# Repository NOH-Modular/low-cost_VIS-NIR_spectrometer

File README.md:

# Low Cost VIS/NIR Spectrometer
We are a team of three students as part of Glasgow University's ENG5026 Design Special Topic 5. This class puts students in groups to initially design a proof of concept and ultimately a product in collaboration with research taking place at the University.

We aim to design a miniaturised, low-cost visible light and near-infrared spectrometer in a handheld form-factor to analyse fruit ripeness and other VIS/NIR applications including use in schools and universities. Existing products are found in the range of between £400-1000 and we aim to produce an alternative which will be more affordable and accessible.

Currently, the project consists of a custom RP2040 microcontroller board with an e-paper display to minimise power draw. The spectral sensing will use AMS-OSRAM's spectral sensor chips which has shown positive results in testing but in order to provide a more robust and elegant solution, additional funding will allow us to experiment with better sensors. The AS7265x triad sensors will give the widest possible range of sensing while still being affordable to the end user.

As well as being low-cost, it is an aim of the project to achieve long battery life for portable use. This is why low-power design such as battery management and an e-paper display has been at the forefront of component choice.

The final output (a PCB with surface-mount components pre-assembled) will be very low-cost, but we require funding for prototyping and testing various spectrometer chips, battery management, microcontrollers, and LEDs.

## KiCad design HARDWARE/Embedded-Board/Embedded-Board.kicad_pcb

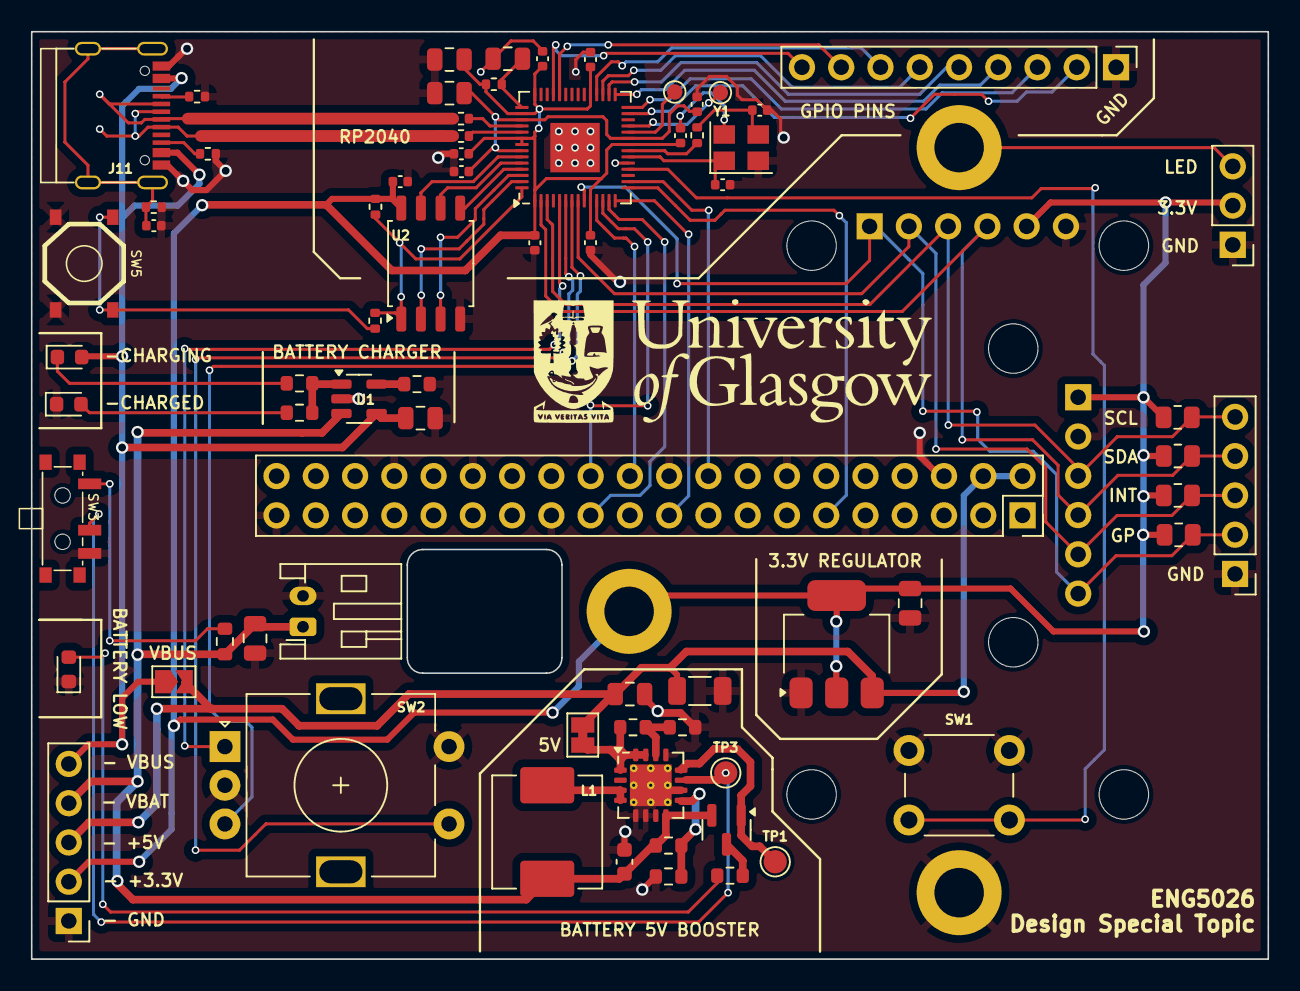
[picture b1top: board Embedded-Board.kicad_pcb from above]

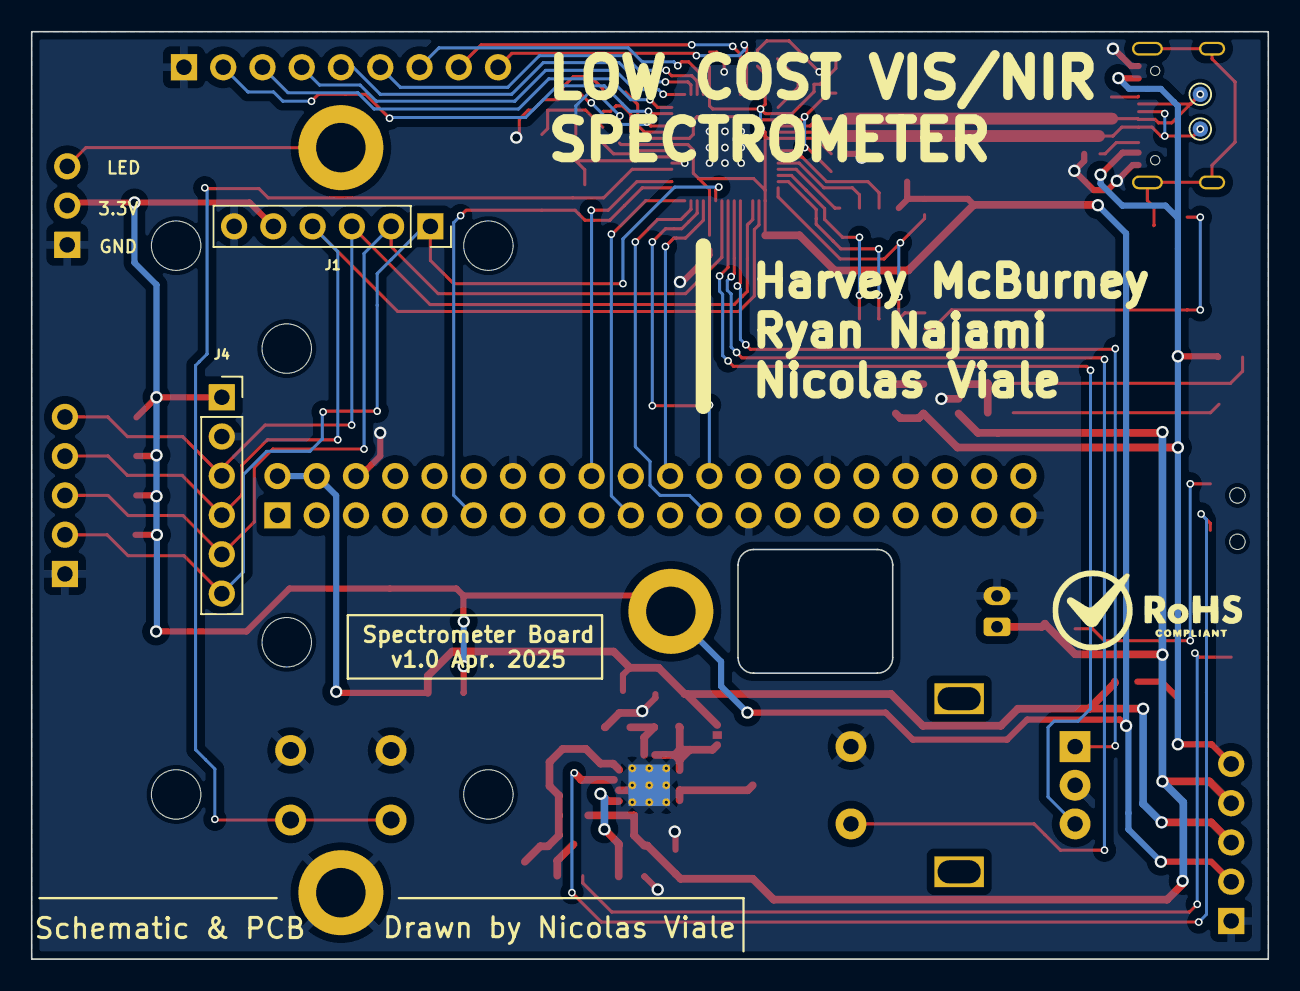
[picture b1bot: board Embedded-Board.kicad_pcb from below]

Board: 2 copper layers, 80.0 x 60.0 mm, 75 parts (4 on the bottom side), 61 nets.

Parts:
BT1: Battery_Cell; JST_PH_S2B-PH-K_1x02_P2.00mm_Horizontal
C2, C3, C58: 10u; C_0805_2012Metric
C4: 100n; C_0603_1608Metric
C5, C13, C14, C21: 2.2u; C_0805_2012Metric
C6: 100u/6V; C_1206_3216Metric
C8, C11, C12, C15, C16, C17, C18, C19, C20, C34: 100n; C_0402_1005Metric
C48, C68: 33p; C_0402_1005Metric
D1: orange; LED_0603_1608Metric
D2: green; LED_0603_1608Metric
D3: red; LED_0603_1608Metric
J1: AD7265X; PinSocket_1x06_P2.54mm_Vertical
J2: POWER-pins; PinHeader_1x05_P2.54mm_Vertical
J3: Conn_02x20_Odd_Even; PinSocket_2x20_P2.54mm_Vertical
J4: AD7341; PinSocket_1x06_P2.54mm_Vertical
J5: I2C comm; PinHeader_1x05_P2.54mm_Vertical
J6: GPIO PINS; PinHeader_1x09_P2.54mm_Vertical
J7: BOARD->LED; PinHeader_1x03_P2.54mm_Vertical
J11: USB_C_Receptacle_USB2.0; USB-C-JLCPCB
JP1: VBUS-5V; SolderJumper-2_P1.3mm_Open_TrianglePad1.0x1.5mm
JP2: OUT-5V; SolderJumper-2_P1.3mm_Bridged_Pad1.0x1.5mm
L1: 6.8u; L_APV_APH0630
Q1: MMUN2133LT1G; SOT-23
R1, R2, R21, R22: 4.7k; R_0805_2012Metric
R3: 10k; R_0402_1005Metric
R4, R5: 1k; R_0402_1005Metric
R6: 470; R_0603_1608Metric
R7: 200; R_0402_1005Metric
R8, R20: 1k; R_0603_1608Metric
R9: 2k; R_0603_1608Metric
R10, R18: 1.85M; R_0603_1608Metric
R11, R17: 340k; R_0603_1608Metric
R12: 220; R_0402_1005Metric
R13, R14: 5.1k; R_0402_1005Metric
R15, R16: 27; R_0402_1005Metric
R19: 200k; R_0603_1608Metric
SW1: SW_Push; SW_PUSH_6mm_H13mm
SW2: RotaryEncoder_Switch; RotaryEncoder_Alps_EC11E-Switch_Vertical_H20mm
SW3: SW_Push_SPDT; Alps-Alpine-SPDT
SW5: BOOT; JLC-BASIC-BUTTON
TP1: LBO; TestPoint_Pad_D1.5mm
TP3: EN; TestPoint_Pad_D1.5mm
TP4: D-; TestPoint_Pad_D1.0mm
TP5: D+; TestPoint_Pad_D1.0mm
TP6: SWCLK; TestPoint_Pad_D1.0mm
TP7: SWD; TestPoint_Pad_D1.0mm
U1: MCP73831-2-OT; SOT-23-5
U2: W25Q16JVS; SOIC-8_5.3x5.3mm_P1.27mm
U3: RP2040; QFN-56-1EP_7x7mm_P0.4mm_EP3.2x3.2mm
U4: TPS61090; Texas_RSA_VQFN-16-1EP_4x4mm_P0.65mm_EP2.7x2.7mm_ThermalVias
U18: LM1117-3.3; SOT-223-3_TabPin2
Y1: 12MHz; Crystal_SMD_3225-4Pin_3.2x2.5mm

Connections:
+1V1: C11.1, C12.1, C13.1, U3.23 (DVDD), U3.45 (VREG_VOUT), U3.50 (DVDD)
+3.3V: C8.1, C14.1, C15.1, C16.1, C17.1, C18.1, C19.1, C20.1, C58.1, J1.5, J2.2, J4.1, J7.2, R1.1, R2.1, R3.1, R7.1, R21.1, R22.1, U2.8 (VCC), U3.1 (IOVDD), U3.10 (IOVDD), U3.22 (IOVDD), U3.33 (IOVDD), U3.42 (IOVDD), U3.44 (VREG_IN), U3.48 (USB_VDD), U3.49 (IOVDD), U18.2 (VO)
+5V: C5.1, C6.1, J2.3, J3.2, J3.4, JP1.2 (B), JP2.2 (B), U18.3 (VI)
+VBAT: BT1.1 (+), C3.1, C4.1, J2.4, L1.1, Q1.2 (E), R10.2, R17.2, U1.3 (V_{BAT}), U4.8 (VBAT)
E-PAPER-BUSY: J3.18, U3.16 (GPIO13)
E-PAPER-CS: J3.24, U3.12 (GPIO9)
E-PAPER-DC: J3.22, U3.11 (GPIO8)
E-PAPER-MOSI: J3.19, U3.14 (GPIO11)
E-PAPER-RST: J3.11, U3.15 (GPIO12)
E-PAPER-SCK: J3.23, U3.13 (GPIO10)
ENC-A: SW2.A, U3.5 (GPIO3)
ENC-B: SW2.B, U3.7 (GPIO5)
ENC-PSH: SW2.S1, U3.6 (GPIO4)
GND: BT1.2 (-), C2.2, C3.2, C4.2, C5.2, C6.2, C8.2, C11.2, C12.2, C13.2, C14.2, C15.2, C16.2, C17.2, C18.2, C19.2, C20.2, C21.2, C34.2, C48.1, C58.2, C68.2, D2.1 (K), D3.1 (K), J1.6, J2.1, J3.6, J3.9, J3.14, J3.20, J3.25, J3.30, J3.34, J3.39, J4.2, J5.1, J6.1, J7.1, J11.A1 (GND), J11.B1 (GND), R9.2, R11.1, R12.2, R13.2, R14.1, R19.2, SW1.1, SW2.C, SW2.S2, SW3.3 (C), SW5.2, U1.2 (V_{SS}), U2.4 (GND), U3.19 (TESTEN), U3.57 (GND), U4.5 (PGND), U4.6 (PGND), U4.7 (PGND), U4.10 (SYNC), U4.13 (GND), U4.17 (PAD), U18.1 (GND), Y1.2, Y1.4
unnamed: C68.1, R5.1, Y1.3
unnamed: D1.1 (K), R6.1
unnamed: D2.2 (A), R8.1
unnamed: D3.2 (A), R20.2
unnamed: J6.2, U3.27 (GPIO16)
unnamed: J6.3, U3.28 (GPIO17)
unnamed: J6.4, U3.29 (GPIO18)
unnamed: J6.5, U3.30 (GPIO19)
unnamed: J6.6, U3.31 (GPIO20)
unnamed: J6.7, U3.32 (GPIO21)
unnamed: J6.8, U3.38 (GPIO26_ADC0)
unnamed: J6.9, U3.39 (GPIO27_ADC1)
unnamed: J11.A5 (CC1), R13.1
unnamed: J11.B5 (CC2), R14.2
unnamed: J11.A6 (D+), J11.B6 (D+), R16.2, TP5.1
unnamed: J11.A7 (D-), J11.B7 (D-), R15.1, TP4.1
unnamed: C34.1, J11.S1 (SHIELD), R12.1
unnamed: JP2.1 (A), R18.2, U4.1 (VOUT), U4.15 (VOUT), U4.16 (VOUT)
unnamed: L1.2, U4.3 (SW), U4.4 (SW)
unnamed: Q1.1 (B), TP1.1, U4.12 (LBO)
unnamed: Q1.3 (C), R20.1
unnamed: R4.1, SW5.1
unnamed: R17.1, SW3.1 (A)
unnamed: SW3.2 (B), TP3.1, U4.11 (EN)
unnamed: R9.1, U1.5 (PROG)
unnamed: R6.2, R8.2, U1.1 (STAT)
unnamed: U2.6 (CLK), U3.52 (QSPI_SCLK)
unnamed: U2.5 (DI(IO0)), U3.53 (QSPI_SD0)
unnamed: U2.2 (DO(IO1)), U3.55 (QSPI_SD1)
unnamed: U2.3 (IO2), U3.54 (QSPI_SD2)
unnamed: U2.7 (IO3), U3.51 (QSPI_SD3)
unnamed: R3.2, R4.2, U2.1 (~CS), U3.56 (QSPI_SS)
unnamed: C21.1, R7.2, U3.43 (ADC_AVDD)
unnamed: TP6.1, U3.24 (SWCLK)
unnamed: TP7.1, U3.25 (SWD)
unnamed: C48.2, U3.20 (XIN), Y1.1
unnamed: R5.2, U3.21 (XOUT)
unnamed: R18.1, R19.1, U4.14 (FB)
unnamed: R10.1, R11.2, U4.9 (LBI)
PUSH-SWITCH: SW1.2, U3.18 (GPIO15)
SENSOR-INT: J1.2, J4.5, J5.3, R21.2, U3.8 (GPIO6)
SENSOR-RST: J1.1, J4.6, J5.2, R22.2, U3.9 (GPIO7)
SENSOR-SCL: J1.3, J4.3, J5.5, R1.2, U3.3 (GPIO1)
SENSOR-SDA: J1.4, J4.4, J5.4, R2.2, U3.2 (GPIO0)
USB_D+: R16.1, U3.47 (USB_DP)
USB_D-: R15.2, U3.46 (USB_DM)
VBUS: C2.1, D1.2 (A), J2.5, J11.A4 (VBUS), J11.B4 (VBUS), JP1.1 (A), U1.4 (V_{DD})

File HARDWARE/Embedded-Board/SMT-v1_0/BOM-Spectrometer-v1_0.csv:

Comment,Designator,Footprint,LCSC Part Number
Battery_Cell,BT1,Connector_JST:JST_PH_S2B-PH-K_1x02_P2.00mm_Horizontal,C5359610
100n,C4,Capacitor_SMD:C_0603_1608Metric,C14663
100u/6V,C6,Capacitor_SMD:C_1206_3216Metric,C15008
10u,"C2,C3,C58",Capacitor_SMD:C_0805_2012Metric,C15850
USB_C_Receptacle_USB2.0,J11,userr:USB-C-JLCPCB,C165948
6.8u,L1,Inductor_SMD:L_APV_APH0630,C5349706
MMUN2133LT1G,Q1,Package_TO_SOT_SMD:SOT-23,C86182
10k,R3,Resistor_SMD:R_0402_1005Metric,C25744
470,R6,Resistor_SMD:R_0603_1608Metric,C23179
200,R7,Resistor_SMD:R_0402_1005Metric,C25087
2k,R9,Resistor_SMD:R_0603_1608Metric,C22975
220,R12,Resistor_SMD:R_0402_1005Metric,C25091
200k,R19,Resistor_SMD:R_0603_1608Metric,C25811
SW_Push_SPDT,SW3,userr:Alps-Alpine-SPDT,C109335
BOOT,SW5,userr:JLC-BASIC-BUTTON,C318884
MCP73831-2-OT,U1,Package_TO_SOT_SMD:SOT-23-5,C424093
W25Q16JVS,U2,Package_SO:SOIC-8_5.3x5.3mm_P1.27mm,C97521
RP2040,U3,Package_DFN_QFN:QFN-56-1EP_7x7mm_P0.4mm_EP3.2x3.2mm,C2040
TPS61090,U4,Package_DFN_QFN:Texas_RSA_VQFN-16-1EP_4x4mm_P0.65mm_EP2.7x2.7mm_ThermalVias,C206167
LM1117-3.3,U18,Package_TO_SOT_SMD:SOT-223-3_TabPin2,C6186
12MHz,Y1,Crystal:Crystal_SMD_3225-4Pin_3.2x2.5mm,C9002
33p,"C48,C68",Capacitor_SMD:C_0402_1005Metric,C1562
1k,"R4,R5",Resistor_SMD:R_0402_1005Metric,C11702
1k,"R8,R20",Resistor_SMD:R_0603_1608Metric,C21190
1.85M,"R10,R18",Resistor_SMD:R_0603_1608Metric,C325651
340k,"R11,R17",Resistor_SMD:R_0603_1608Metric,C23143
5.1k,"R13,R14",Resistor_SMD:R_0402_1005Metric,C25905
27,"R15,R16",Resistor_SMD:R_0402_1005Metric,C138021
2.2u,"C5,C13,C14,C21",Capacitor_SMD:C_0805_2012Metric,C377773
100n,"C8,C11,C12,C15,C16,C17,C18,C19,C20,C34",Capacitor_SMD:C_0402_1005Metric,C307331

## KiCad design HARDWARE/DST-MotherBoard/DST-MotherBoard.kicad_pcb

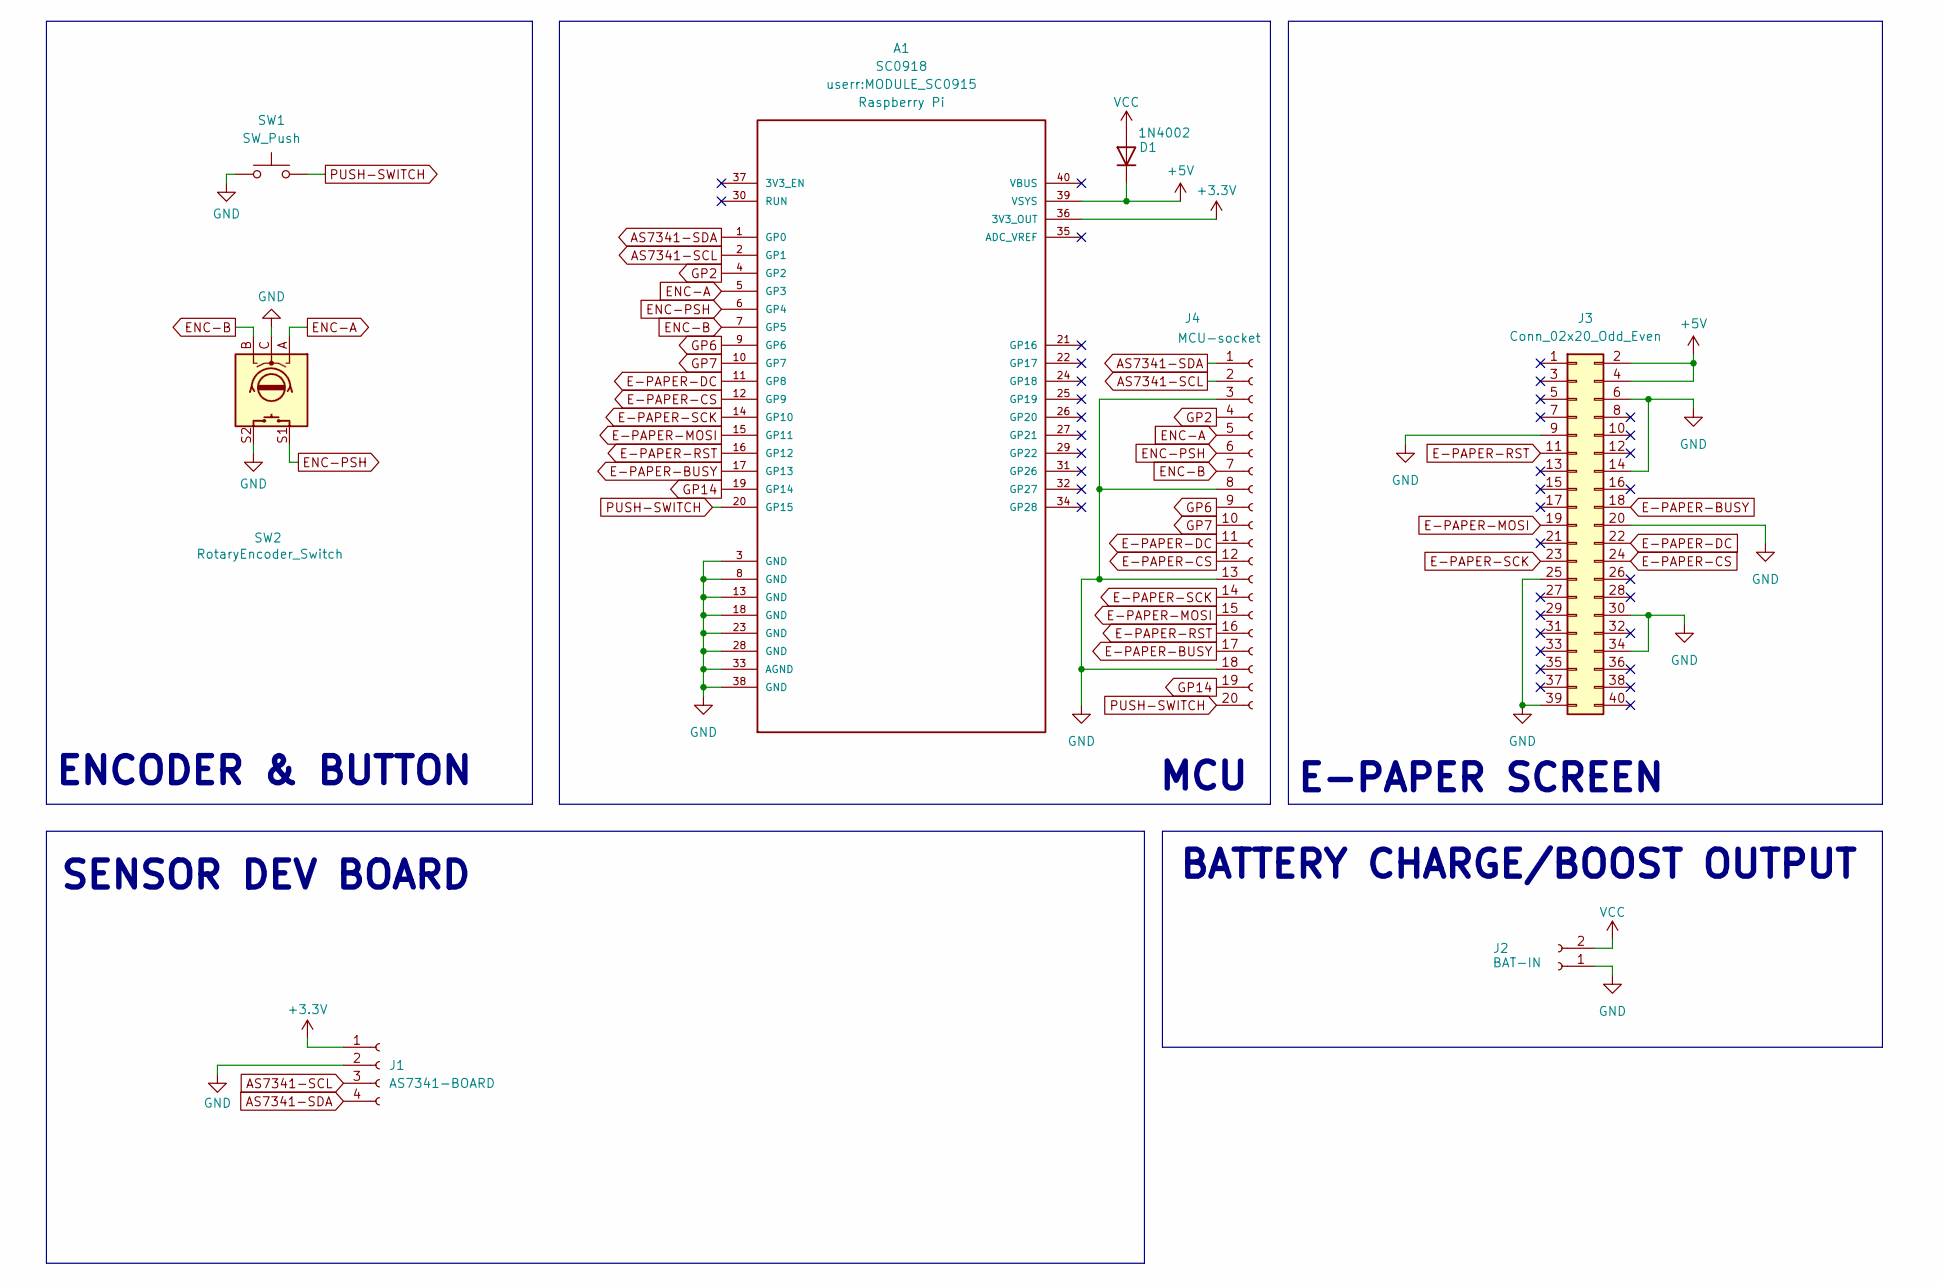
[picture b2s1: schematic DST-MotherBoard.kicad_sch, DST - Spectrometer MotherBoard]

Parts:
A1: SC0918; MODULE_SC0915; PARTREV 1.6
D1: 1N4002; D_DO-41_SOD81_P10.16mm_Horizontal; LCSC C169542
J1: AS7341-BOARD; PinSocket_1x04_P2.54mm_Vertical
J2: BAT-IN; PinSocket_1x02_P2.54mm_Vertical
J3: Conn_02x20_Odd_Even; PinSocket_2x20_P2.54mm_Vertical
J4: MCU-socket; PinHeader_1x20_P2.54mm_Vertical
SW1: SW_Push; SW_PUSH_6mm_H13mm
SW2: RotaryEncoder_Switch; RotaryEncoder_Alps_EC11E-Switch_Vertical_H20mm

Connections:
+3.3V: A1.36 (3V3_OUT), J1.1
+5V: A1.39 (VSYS), D1.1 (K), J3.2, J3.4
AS7341-SCL: A1.2 (GP1), J1.3, J4.2
AS7341-SDA: A1.1 (GP0), J1.4, J4.1
E-PAPER-BUSY: A1.17 (GP13), J3.18, J4.17
E-PAPER-CS: A1.12 (GP9), J3.24, J4.12
E-PAPER-DC: A1.11 (GP8), J3.22, J4.11
E-PAPER-MOSI: A1.15 (GP11), J3.19, J4.15
E-PAPER-RST: A1.16 (GP12), J3.11, J4.16
E-PAPER-SCK: A1.14 (GP10), J3.23, J4.14
ENC-A: A1.5 (GP3), J4.5, SW2.A
ENC-B: A1.7 (GP5), J4.7, SW2.B
ENC-PSH: A1.6 (GP4), J4.6, SW2.S1
GND: A1.3 (GND), A1.8 (GND), A1.13 (GND), A1.18 (GND), A1.23 (GND), A1.28 (GND), A1.33 (AGND), A1.38 (GND), J1.2, J2.1, J3.6, J3.9, J3.14, J3.20, J3.25, J3.30, J3.34, J3.39, J4.3, J4.8, J4.13, J4.18, SW1.1, SW2.C, SW2.S2
GP2: A1.4 (GP2), J4.4
GP6: A1.9 (GP6), J4.9
GP7: A1.10 (GP7), J4.10
GP14: A1.19 (GP14), J4.19
PUSH-SWITCH: A1.20 (GP15), J4.20, SW1.2
VCC: D1.2 (A), J2.2

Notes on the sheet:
E-PAPER SCREEN
ENCODER & BUTTON
MCU
SENSOR DEV BOARD
BATTERY CHARGE/BOOST OUTPUT

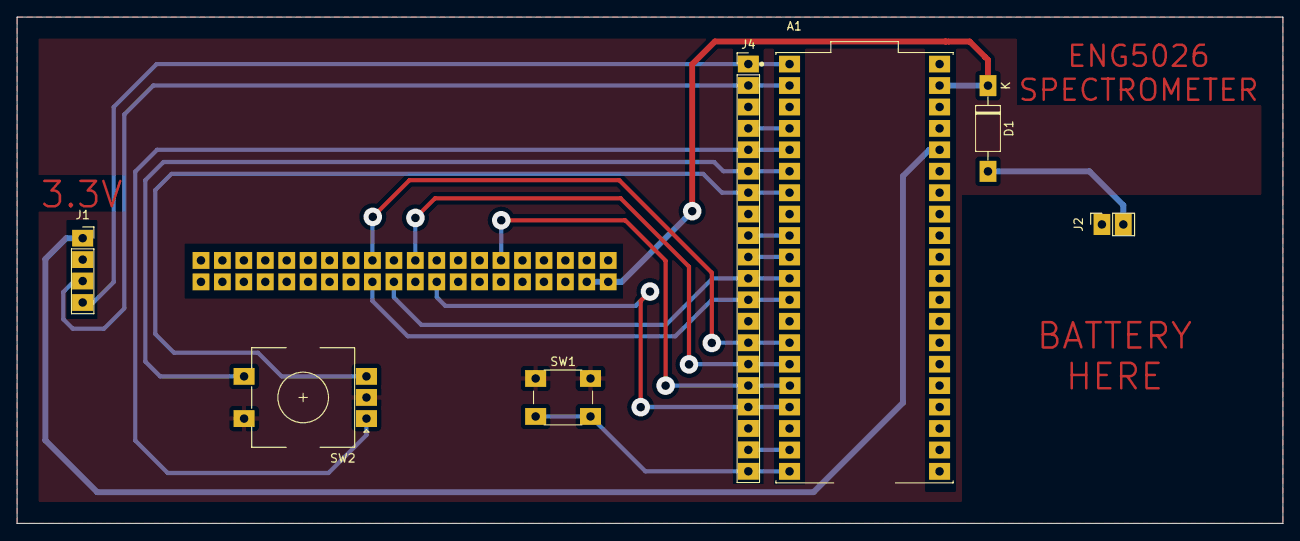
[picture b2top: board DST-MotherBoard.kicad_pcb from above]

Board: 2 copper layers, 150.0 x 60.0 mm, 8 parts (1 on the bottom side), 20 nets.

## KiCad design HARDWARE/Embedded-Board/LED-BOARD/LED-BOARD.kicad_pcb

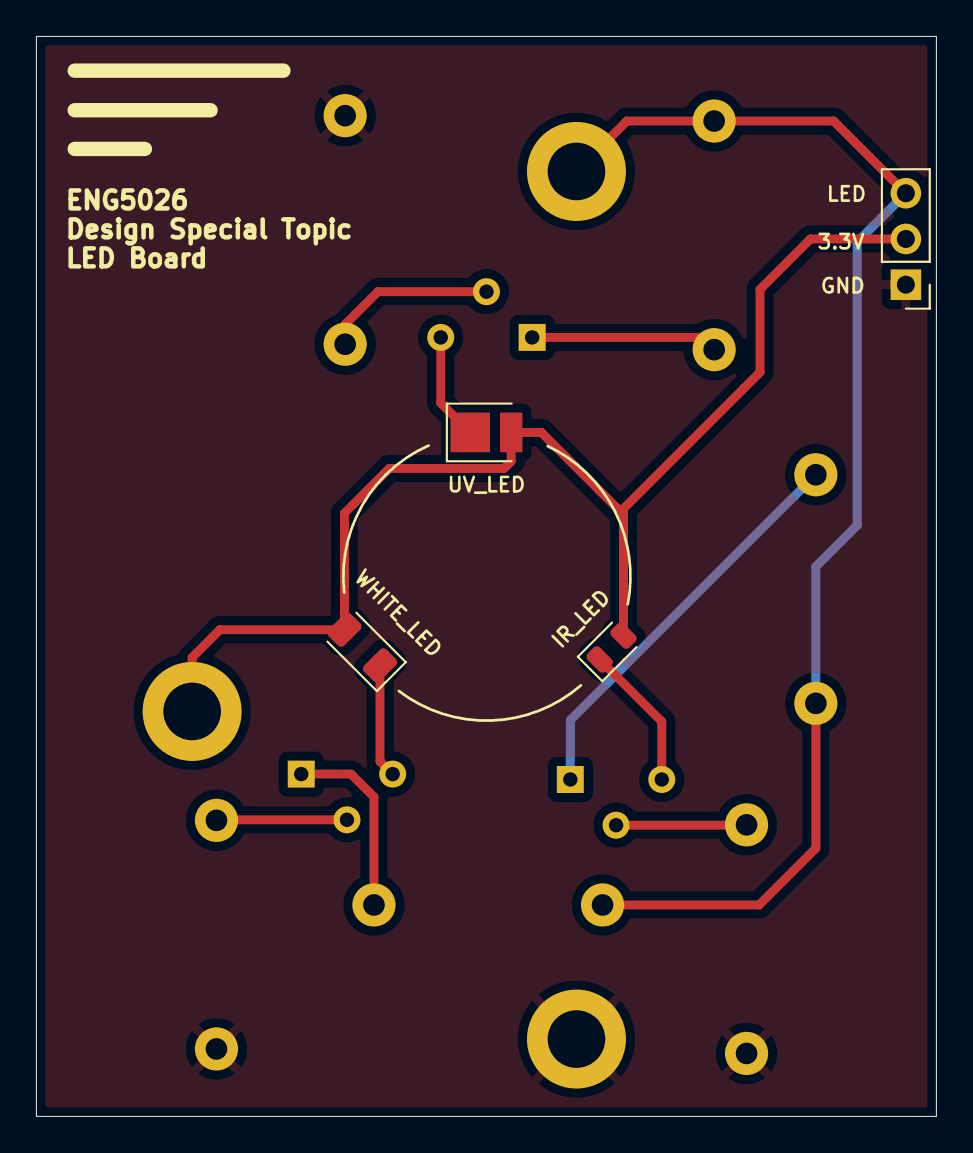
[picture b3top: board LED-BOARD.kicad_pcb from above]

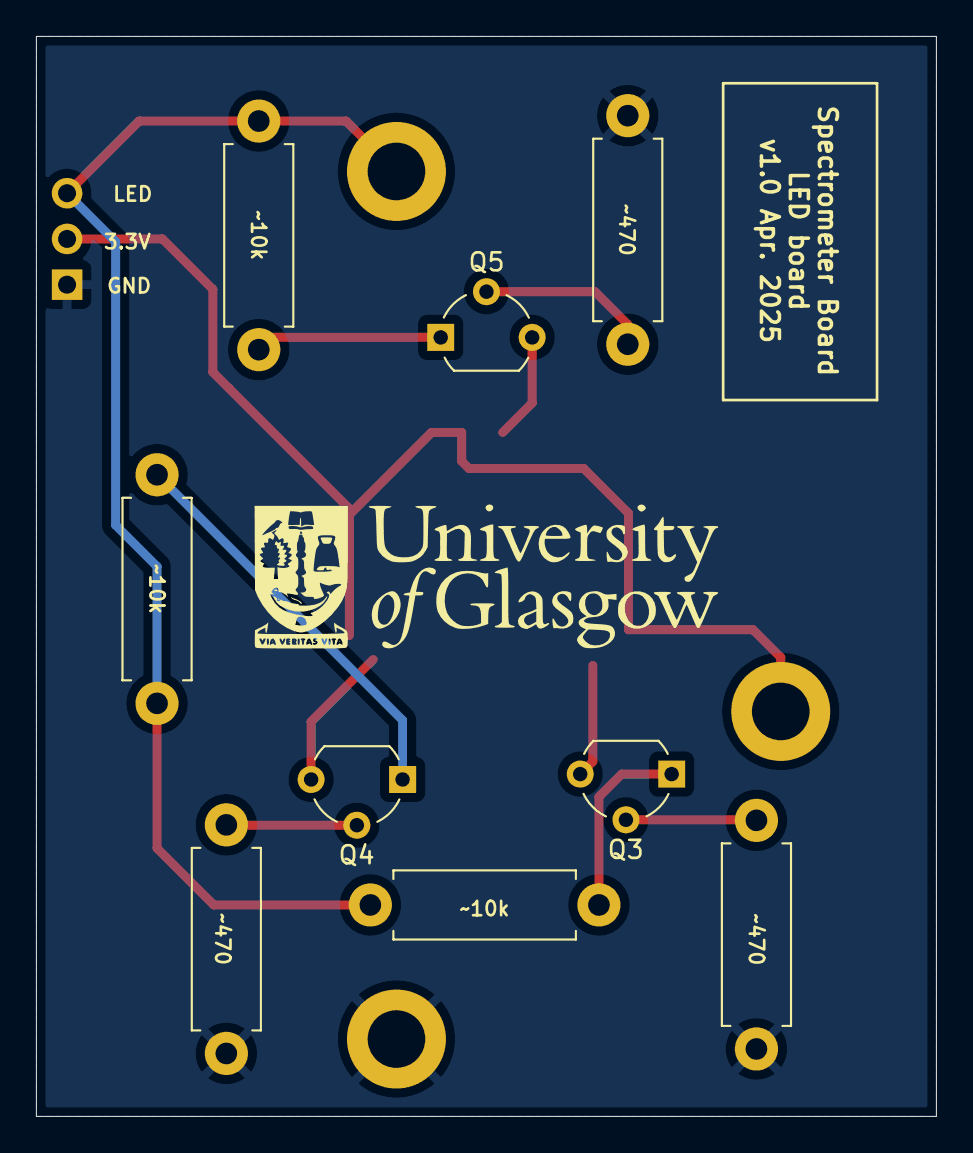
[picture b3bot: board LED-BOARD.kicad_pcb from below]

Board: 2 copper layers, 50.0 x 60.0 mm, 13 parts (9 on the bottom side), 12 nets.

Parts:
D4: WHITE-LED; LED_1206_3216Metric
D5: IR_LED; LED_0805_2012Metric
D6: UV_LED; LED_PLCC_2835
J8: LED->BOARD; PinHeader_1x03_P2.54mm_Vertical
Q3, Q4, Q5: Q_NPN_BEC; TO-92_Wide
R23, R24, R25: 10k; R_Axial_DIN0411_L9.9mm_D3.6mm_P12.70mm_Horizontal
R26, R27, R28: 470; R_Axial_DIN0411_L9.9mm_D3.6mm_P12.70mm_Horizontal

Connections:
+3.3V: D4.2 (A), D5.2 (A), D6.2 (A), J8.2
GND: J8.1, R26.1, R27.1, R28.1
LED-BOARD: J8.3, R23.1, R24.1, R25.1
unnamed: D4.1 (K), Q3.3 (C)
unnamed: D5.1 (K), Q4.3 (C)
unnamed: D6.1 (K), Q5.3 (C)
unnamed: Q3.1 (B), R23.2
unnamed: Q3.2 (E), R26.2
unnamed: Q4.1 (B), R24.2
unnamed: Q4.2 (E), R27.2
unnamed: Q5.1 (B), R25.2
unnamed: Q5.2 (E), R28.2

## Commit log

2025-03-18 initial blob
    folders, readme, and organisation
2025-03-18 added MotherBoard Files
2025-03-18 updated AS7341 code
    not working but weird behavour
2025-03-18 added arduino code
2025-03-18 fixed
2025-04-01 added test code
2025-04-01 I2C works + Prints values
2025-04-08 New Custom Board
    created the KiCad file and started with schematic
2025-04-08 Schematic v1 done
2025-04-08 pdf added
2025-04-08 small fix
2025-04-13 Added modified epd driver
    Modified EPD arduino firmware from waveshare to work with the pinout on pi pico. Original repo is https://github.com/waveshareteam/e-Paper
2025-04-14 Removed unnecessary files
    now builds if you add "src" to an arduino sketch directory
2025-04-15 Changed directory structure so ino can be opened
2025-04-25 Removed old GxEPD2 Test, added working test
2025-04-25 New PCB design for JLCPCB
2025-04-25 small update
2025-04-27 C++ for visualisation using AS7265x
    This is the program used to visualise readings from the AS7265x sensor in the form of a bar chart.
2025-04-29 Final PCB version
2025-04-29 Splitting the Embedded & LED PCBs
2025-04-29 updated BOM
2025-04-29 Board Pictures for the Blog Post
2025-04-30 test with integration
2025-05-01 Working!
2025-05-02 Added encoder and button support
    Now detects when the sensor is connected and shows this on screen at startup.
    Encoder changes between firemode (single, continuous, burst (2-9)). When rotated while switch is pressed, changes LED mode (combinations of internal and external on/off).
    Button will trigger a reading but haven't bound interrupt yet.
2025-05-08 trying to get controls working
2025-05-09 Created new Firmware
    Changes most of how things work, can't comment on sensor compatibility yet but should be easier to understand. Encoder doesn't register yet and for some reason pressing the button takes two readings 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
    Still don't know exactly how to do the averaging but shouldn't be hard, and this uses full refreshes for everything but it's fast enough. This might need to change for the encoder though.
2025-05-12 fixed i2c
2025-05-12 switch to rotaryencoder lub
2025-05-16 Initial Refactor
    Moved declarations and definitions to external cpp and h files. No additional functionality yet.
2025-05-16 AS7431 Working
    Added new screen for displaying results from AS7341, automatically sets based on which sensor is detected. Input issues remain and the colour detection hasn't been updated for AS7341 yet.
2025-05-16 3D CASE - v1
2025-05-17 fixed many issues, more reponsive
    everything apart from exiting continuous mode and encoder control works!
2025-05-17 Fixed colour detection, simplified comments
2025-05-20 Ripeness scale, no calculation yet
2025-05-20 firmware-v1_1
2025-05-20 working with real banana
2025-05-20 continuous mode attempt
    the issue now is that the timer does not enable itself when it is supposed to, nor does it disable itself when force enabled.
2025-05-21 CONTINUUOUS WORKS!
2025-05-21 merged new io code with ripeness code, still needs mode switch
2025-05-21 adjusted gain for AS7341 to 32x from 256x
2025-05-21 fixed ripeness function, disabled UV LED
2025-05-23 added the sustainability assessment
